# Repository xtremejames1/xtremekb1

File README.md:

# xtremekb1
## A custom ergonomic keyboard
**WIP**

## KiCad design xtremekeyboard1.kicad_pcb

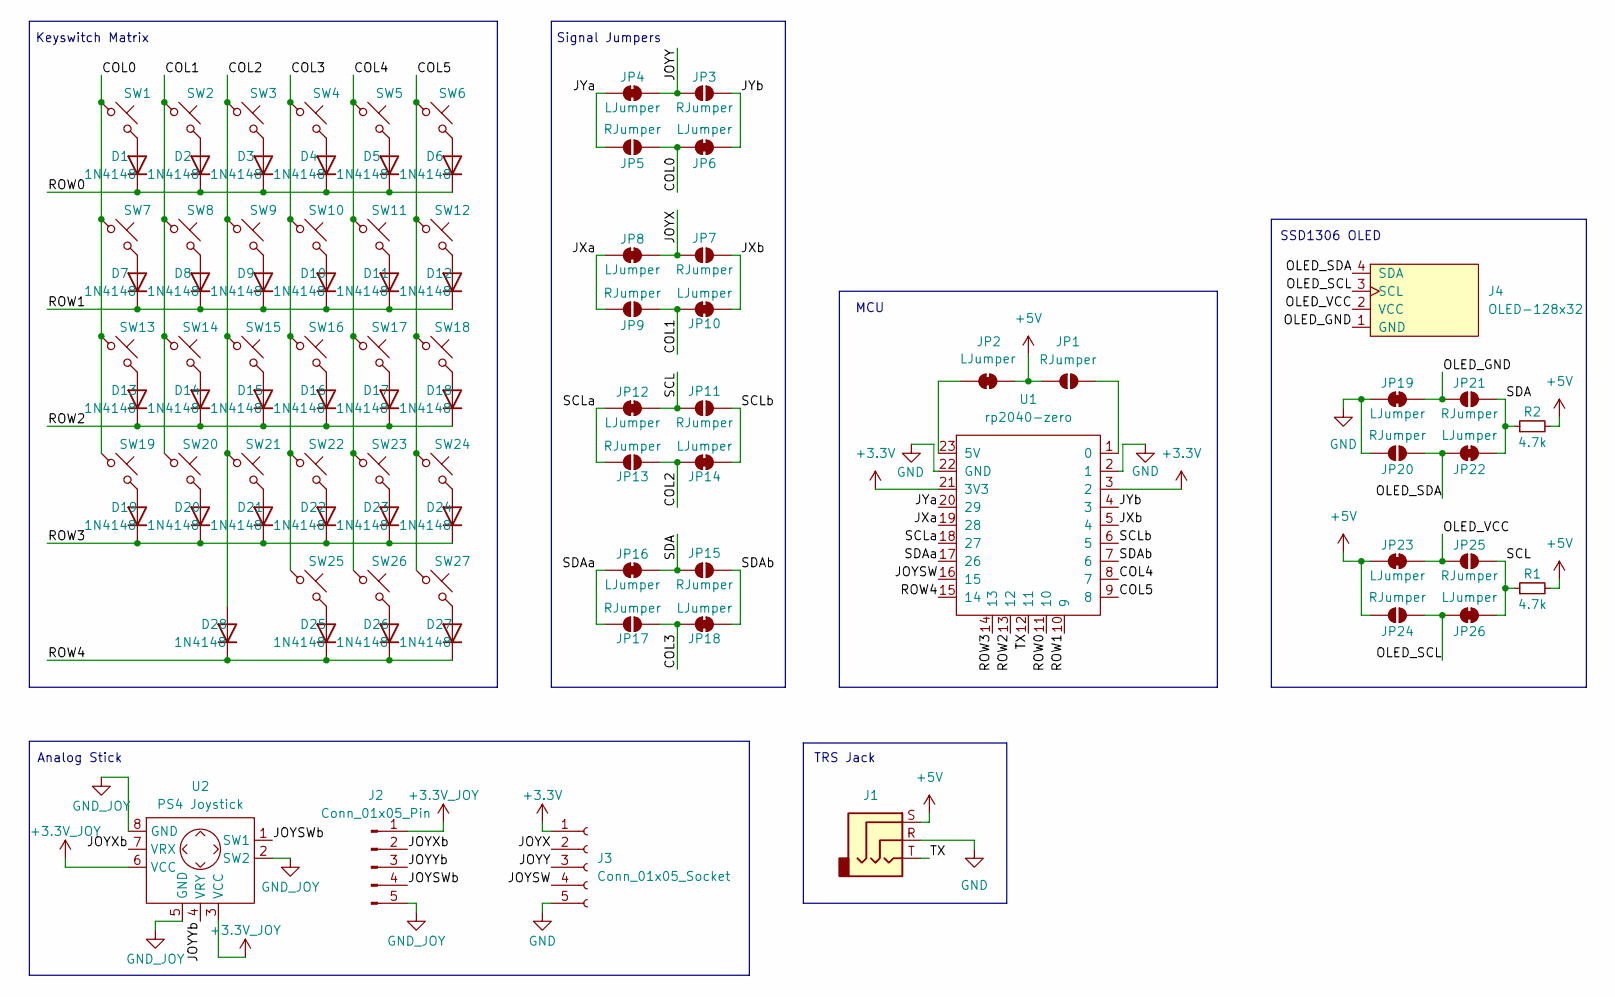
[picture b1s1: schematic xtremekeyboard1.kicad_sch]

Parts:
D1, D2, D3, D4, D5, D6, D7, D8, D9, D10, D11, D12, D13, D14, D15, D16, D17, D18, D19, D20, D21, D22, D23, D24, D25, D26, D27, D28: 1N4148; D_DO-35_SOD27_P7.62mm_Horizontal
J1: PJ316 TRS
J2: Conn_01x05_Pin; 5_Solder_Pad
J3: Conn_01x05_Socket; 5_Solder_Pad
J4: OLED-128x32; OLED-128x32-cutout
JP1, JP3, JP5, JP7, JP9, JP11, JP13, JP15, JP17, JP20, JP21, JP24, JP25: RJumper; SolderJumper-2_P1.3mm_Open_TrianglePad1.0x1.5mm
JP2, JP4, JP6, JP8, JP10, JP12, JP14, JP16, JP18, JP19, JP22, JP23, JP26: LJumper; SolderJumper-2_P1.3mm_Open_TrianglePad1.0x1.5mm
R1, R2: 4.7k; R_Axial_DIN0204_L3.6mm_D1.6mm_P5.08mm_Horizontal
SW1, SW2, SW3, SW4, SW5, SW6, SW7, SW8, SW9, SW10, SW11, SW12, SW13, SW14, SW15, SW16, SW17, SW18, SW19, SW20, SW21, SW22, SW23, SW24, SW25, SW26, SW27: 1u MX; MX_PCB_Reversible
U1: rp2040-zero; rp2040-zero-tht
U2: PS4 Joystick; PS4_joystick

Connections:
+3.3V: J3.1, U1.3 (2), U1.21 (3V3)
+3.3V_JOY: J2.1, U2.3 (VCC), U2.6 (VCC)
+5V: J1.S, JP1.2 (B), JP2.2 (B), JP23.2 (B), JP24.2 (B), R1.2, R2.2
/COL0: JP5.1 (A), JP6.1 (A), SW1.1, SW7.1, SW13.1, SW19.1
/COL1: JP9.1 (A), JP10.1 (A), SW2.1, SW8.1, SW14.1, SW20.1
/COL2: D28.2 (A), JP13.1 (A), JP14.1 (A), SW3.1, SW9.1, SW15.1, SW21.1
/COL3: JP17.1 (A), JP18.1 (A), SW4.1, SW10.1, SW16.1, SW22.1, SW25.1
/COL4: SW5.1, SW11.1, SW17.1, SW23.1, SW26.1, U1.8 (7)
/COL5: SW6.1, SW12.1, SW18.1, SW24.1, SW27.1, U1.9 (8)
/JOYSW: J3.4, U1.16 (15)
/JOYSWb: J2.4, U2.1 (SW1)
/JOYX: J3.2, JP7.1 (A), JP8.1 (A)
/JOYXb: J2.2, U2.7 (VRX)
/JOYY: J3.3, JP3.1 (A), JP4.1 (A)
/JOYYb: J2.3, U2.4 (VRY)
/JXa: JP8.2 (B), JP9.2 (B), U1.19 (28)
/JXb: JP7.2 (B), JP10.2 (B), U1.5 (4)
/JYa: JP4.2 (B), JP5.2 (B), U1.20 (29)
/JYb: JP3.2 (B), JP6.2 (B), U1.4 (3)
/OLED_GND: J4.1 (GND), JP19.1 (A), JP21.1 (A)
/OLED_SCL: J4.3 (SCL), JP24.1 (A), JP26.1 (A)
/OLED_SDA: J4.4 (SDA), JP20.1 (A), JP22.1 (A)
/OLED_VCC: J4.2 (VCC), JP23.1 (A), JP25.1 (A)
/ROW0: D1.1 (K), D2.1 (K), D3.1 (K), D4.1 (K), D5.1 (K), D6.1 (K), U1.11 (10)
/ROW1: D7.1 (K), D8.1 (K), D9.1 (K), D10.1 (K), D11.1 (K), D12.1 (K), U1.10 (9)
/ROW2: D13.1 (K), D14.1 (K), D15.1 (K), D16.1 (K), D17.1 (K), D18.1 (K), U1.13 (12)
/ROW3: D19.1 (K), D20.1 (K), D21.1 (K), D22.1 (K), D23.1 (K), D24.1 (K), U1.14 (13)
/ROW4: D25.1 (K), D26.1 (K), D27.1 (K), D28.1 (K), U1.15 (14)
/SCL: JP11.1 (A), JP12.1 (A), JP25.2 (B), JP26.2 (B), R1.1
/SCLa: JP12.2 (B), JP13.2 (B), U1.18 (27)
/SCLb: JP11.2 (B), JP14.2 (B), U1.6 (5)
/SDA: JP15.1 (A), JP16.1 (A), JP21.2 (B), JP22.2 (B), R2.1
/SDAa: JP16.2 (B), JP17.2 (B), U1.17 (26)
/SDAb: JP15.2 (B), JP18.2 (B), U1.7 (6)
/TX: J1.T, U1.12 (11)
GND: J1.R, J3.5, JP19.2 (B), JP20.2 (B), U1.2 (1), U1.22 (GND)
GND_JOY: J2.5, U2.2 (SW2), U2.5 (GND), U2.8 (GND)
unnamed: D1.2 (A), SW1.2
unnamed: D2.2 (A), SW2.2
unnamed: D3.2 (A), SW3.2
unnamed: D4.2 (A), SW4.2
unnamed: D5.2 (A), SW5.2
unnamed: D6.2 (A), SW6.2
unnamed: D7.2 (A), SW7.2
unnamed: D8.2 (A), SW8.2
unnamed: D9.2 (A), SW9.2
unnamed: D10.2 (A), SW10.2
unnamed: D11.2 (A), SW11.2
unnamed: D12.2 (A), SW12.2
unnamed: D13.2 (A), SW13.2
unnamed: D14.2 (A), SW14.2
unnamed: D15.2 (A), SW15.2
unnamed: D16.2 (A), SW16.2
unnamed: D17.2 (A), SW17.2
unnamed: D18.2 (A), SW18.2
unnamed: D19.2 (A), SW19.2
unnamed: D20.2 (A), SW20.2
unnamed: D21.2 (A), SW21.2
unnamed: D22.2 (A), SW22.2
unnamed: D23.2 (A), SW23.2
unnamed: D24.2 (A), SW24.2
unnamed: D25.2 (A), SW25.2
unnamed: D26.2 (A), SW26.2
unnamed: D27.2 (A), SW27.2
unnamed: JP1.1 (A), U1.1 (0)
unnamed: JP2.1 (A), U1.23 (5V)

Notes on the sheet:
SSD1306 OLED
Keyswitch Matrix
Signal Jumpers
MCU
Analog Stick
TRS Jack

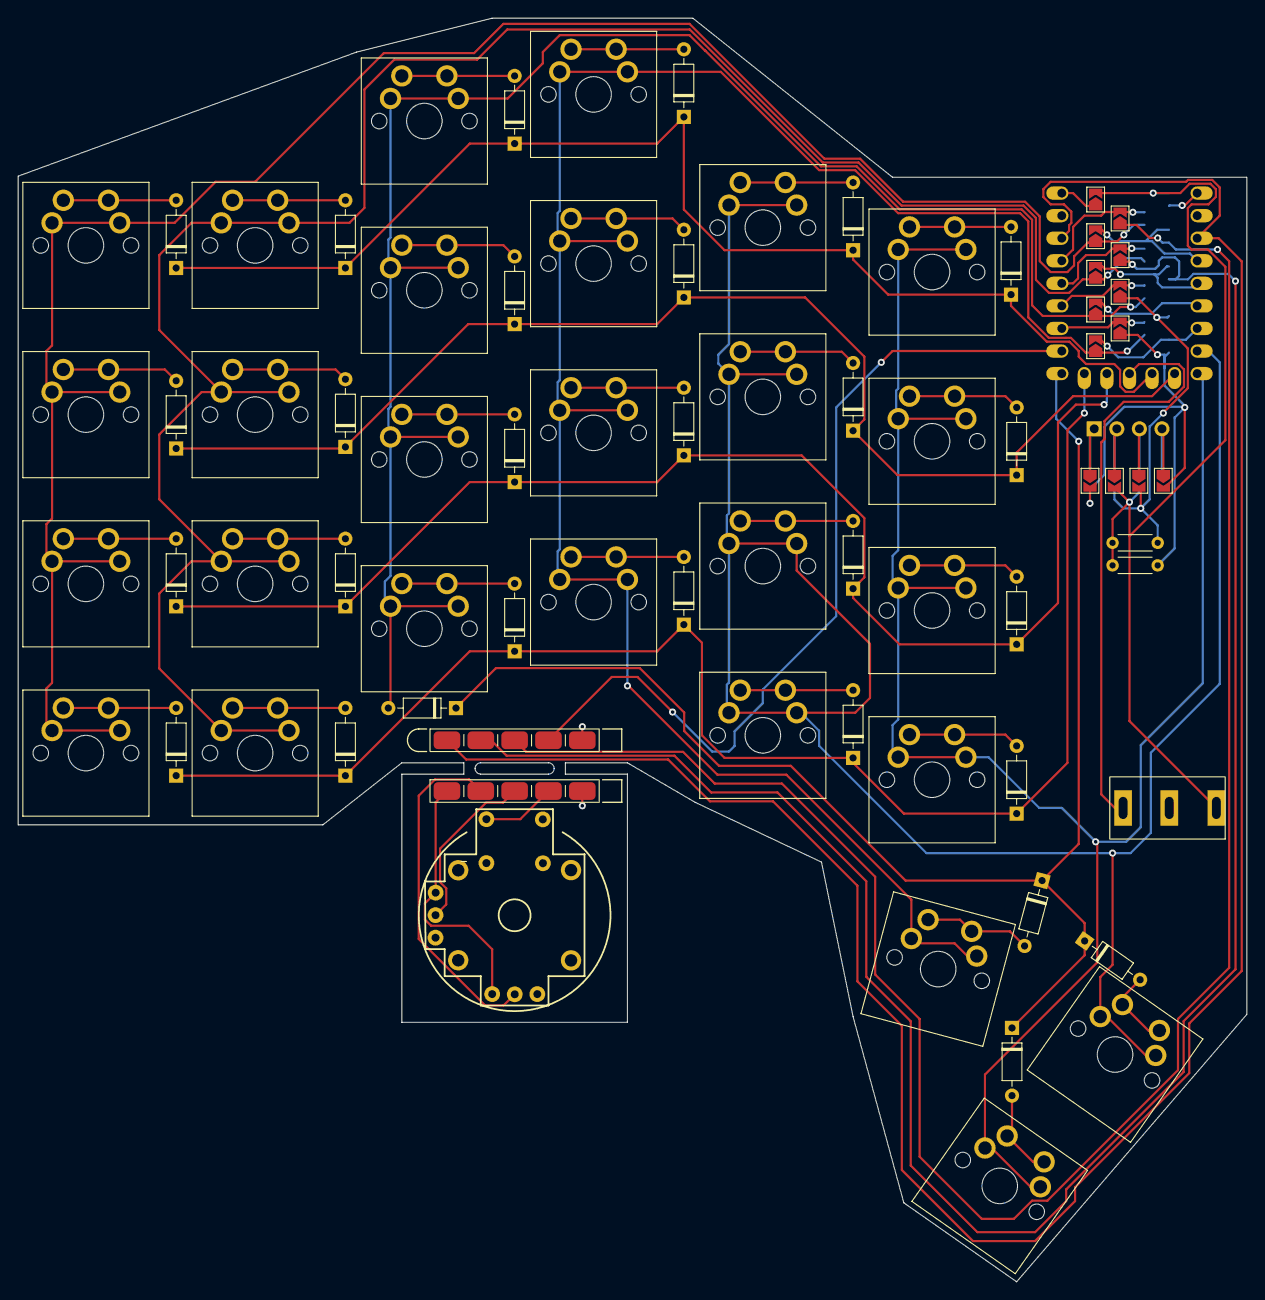
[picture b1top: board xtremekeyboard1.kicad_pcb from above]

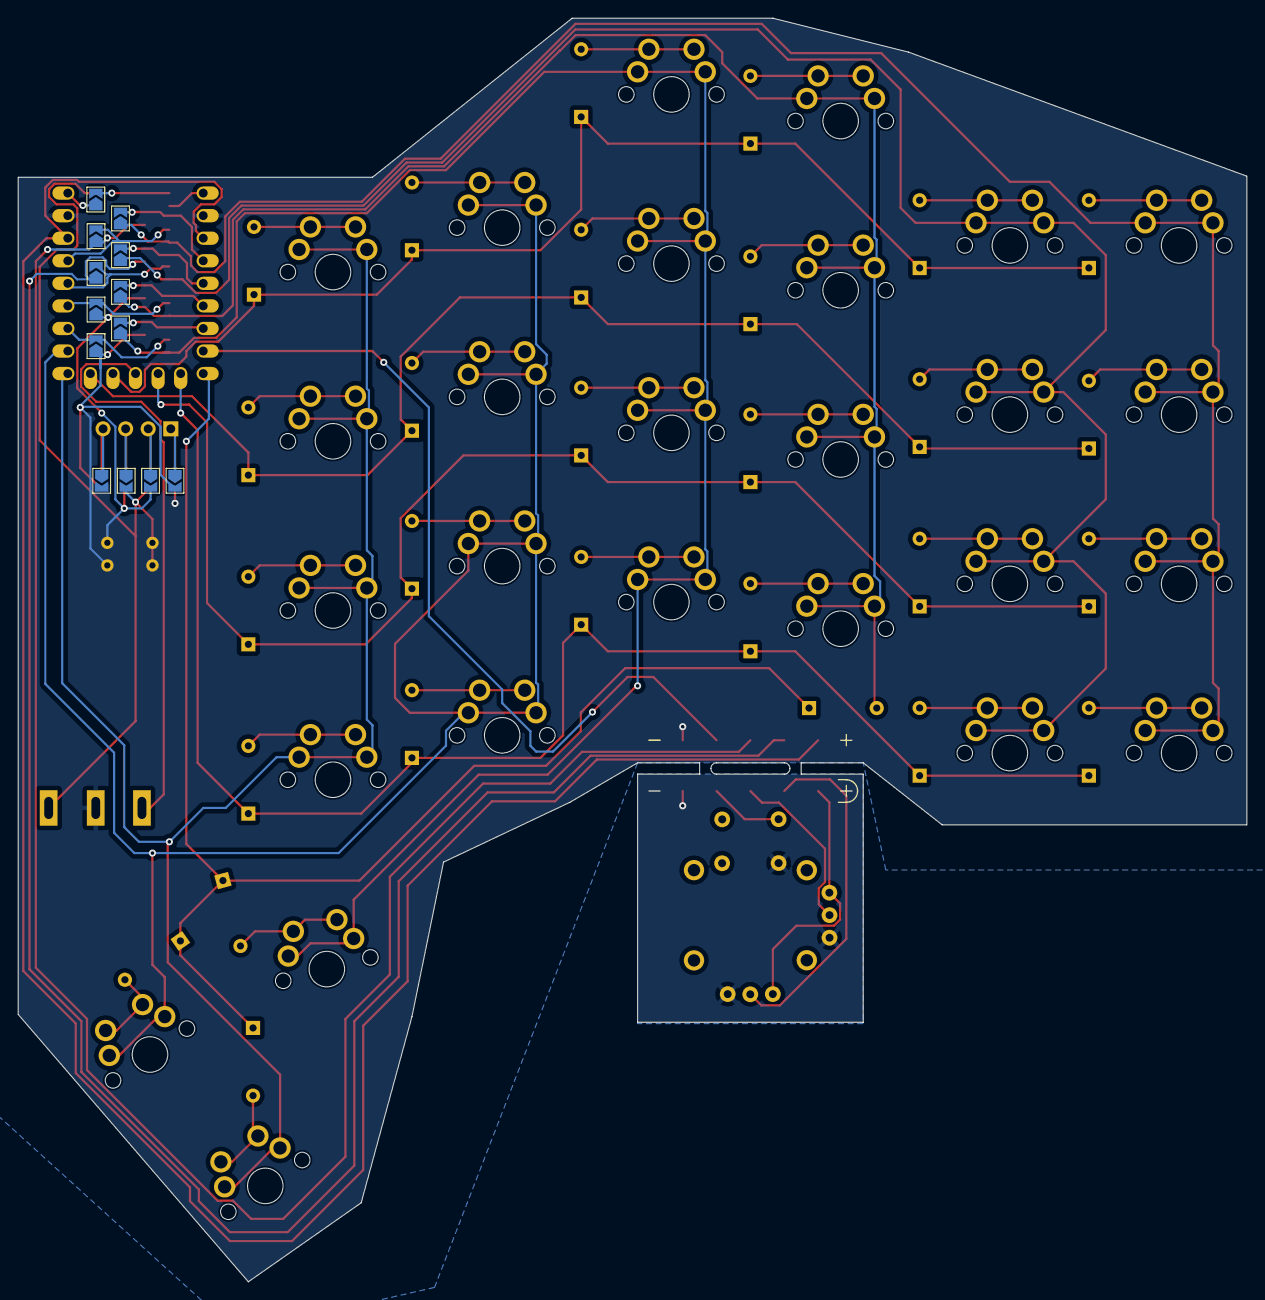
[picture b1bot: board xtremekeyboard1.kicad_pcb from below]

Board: 2 copper layers, 138.3 x 142.2 mm, 89 parts (13 on the bottom side), 66 nets.

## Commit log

2024-03-29 added files
2024-03-29 edited readme
2024-03-29 pushing slight changes
2024-04-01 version 1, no display
2024-04-01 finished pcb routing
2024-04-02 finished good pcb, need to make oled reversible, maybe put jumpers on respective side
2024-04-04 added pullup resistors, fixed solder jumpers
2024-04-10 finished PCB i think
2024-04-10 Polished up models, fixed step export
